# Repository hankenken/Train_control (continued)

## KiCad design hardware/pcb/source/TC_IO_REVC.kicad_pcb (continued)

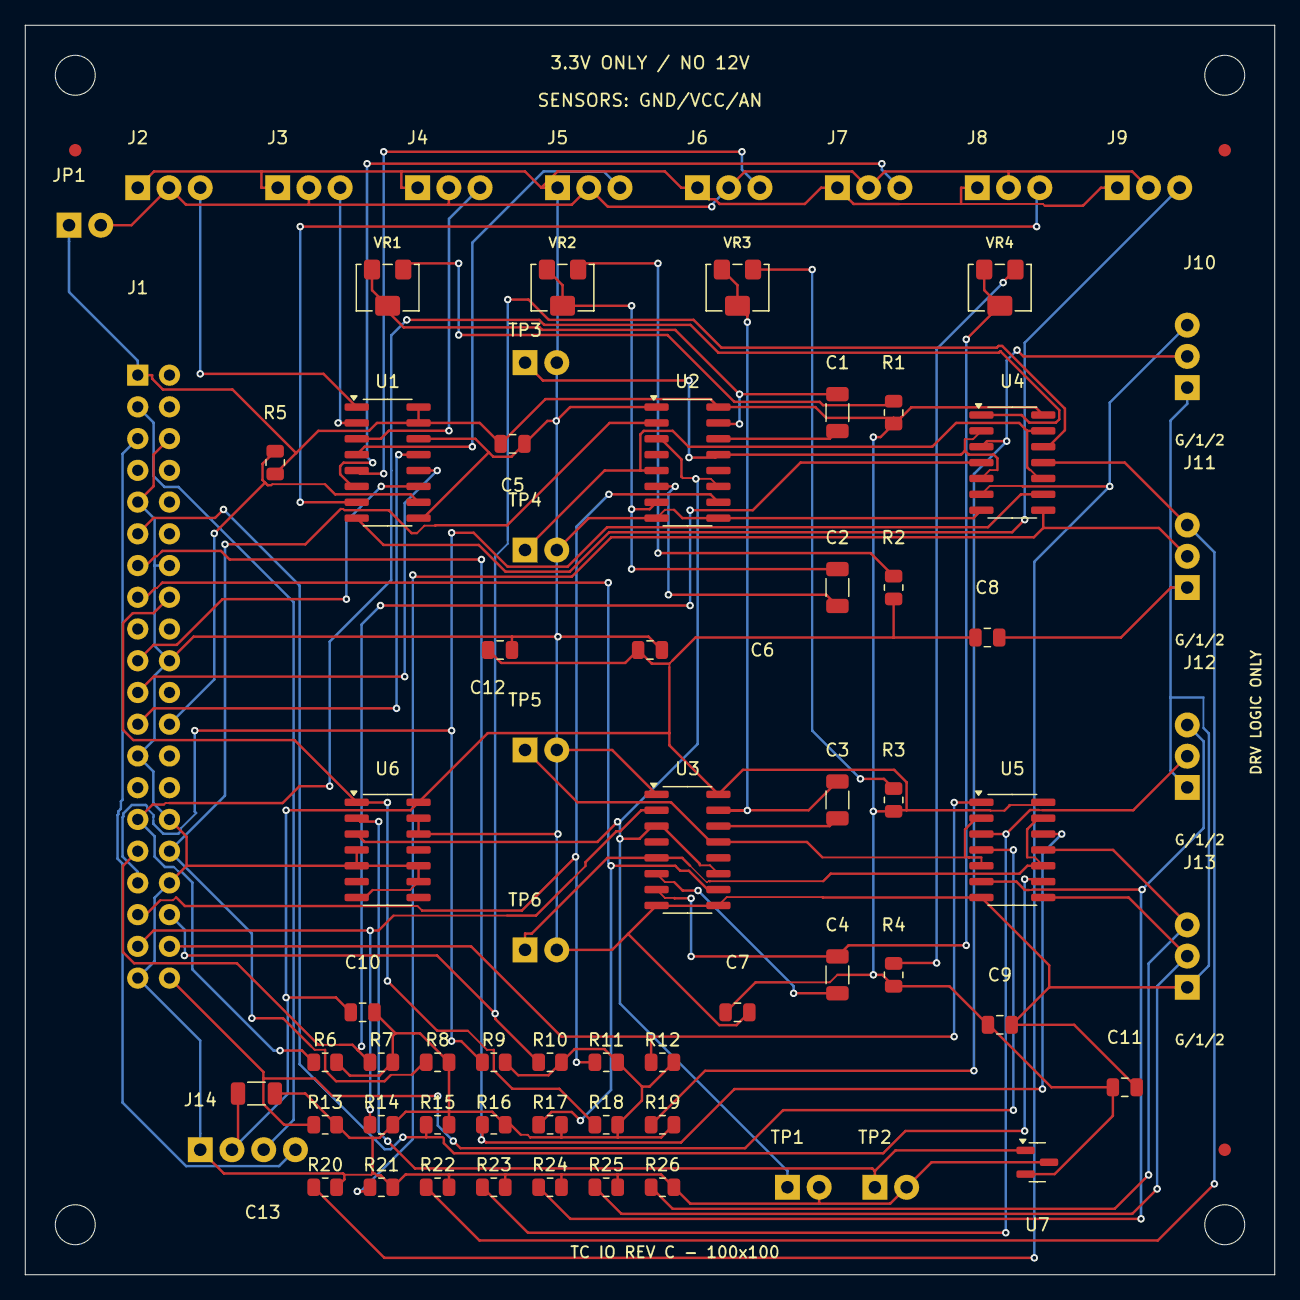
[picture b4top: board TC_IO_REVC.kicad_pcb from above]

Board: 2 copper layers, 100.0 x 100.0 mm, 78 parts (0 on the bottom side), 56 nets.

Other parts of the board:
FM1, FM2, FM3: Fiducial_1mm_Mask2mm
H1, H2, H3, H4: MountingHole_3.2mm_M3

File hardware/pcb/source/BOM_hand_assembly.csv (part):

Reference,Value_or_MPN,Footprint,Quantity,Notes,Populate
J1,WIRE_PADS_NO_COMPONENT,TC_Wire:WirePads_2x20_P2.54,0,Plated wire/test pads only. No connector or header component is fitted.,no
J2,WIRE_PADS_NO_COMPONENT,TC_Wire:WirePads_1x03_P2.50,0,Plated wire/test pads only. No connector or header component is fitted.,no
J3,WIRE_PADS_NO_COMPONENT,TC_Wire:WirePads_1x03_P2.50,0,Plated wire/test pads only. No connector or header component is fitted.,no
J4,WIRE_PADS_NO_COMPONENT,TC_Wire:WirePads_1x03_P2.50,0,Plated wire/test pads only. No connector or header component is fitted.,no
J5,WIRE_PADS_NO_COMPONENT,TC_Wire:WirePads_1x03_P2.50,0,Plated wire/test pads only. No connector or header component is fitted.,no
J6,WIRE_PADS_NO_COMPONENT,TC_Wire:WirePads_1x03_P2.50,0,Plated wire/test pads only. No connector or header component is fitted.,no
J7,WIRE_PADS_NO_COMPONENT,TC_Wire:WirePads_1x03_P2.50,0,Plated wire/test pads only. No connector or header component is fitted.,no
J8,WIRE_PADS_NO_COMPONENT,TC_Wire:WirePads_1x03_P2.50,0,Plated wire/test pads only. No connector or header component is fitted.,no
J9,WIRE_PADS_NO_COMPONENT,TC_Wire:WirePads_1x03_P2.50,0,Plated wire/test pads only. No connector or header component is fitted.,no
JP1,WIRE_PADS_NO_COMPONENT,TC_Wire:WirePads_1x02_P2.54,0,Plated wire/test pads only. No connector or header component is fitted.,no
U1,MCP3008T-I/SL,Package_SO:SOIC-16_3.9x9.9mm_P1.27mm,1,"10-bit ADC, 3.3V supply/reference; sensor outputs must stay within 0..3.3V",yes
U2,CD74HC221M96,Package_SO:SOIC-16_3.9x9.9mm_P1.27mm,1,"HC, NOT LS/HCT. Timing RC unverified at 3.3V: measure before load connection",yes
U3,CD74HC221M96,Package_SO:SOIC-16_3.9x9.9mm_P1.27mm,1,"HC, NOT LS/HCT. Timing RC unverified at 3.3V: measure before load connection",yes
U4,SN74HC08DR,Package_SO:SOIC-14_3.9x8.7mm_P1.27mm,1,,yes
U5,SN74HC08DR,Package_SO:SOIC-14_3.9x8.7mm_P1.27mm,1,,yes
U6,SN74HC08DR,Package_SO:SOIC-14_3.9x8.7mm_P1.27mm,1,,yes
U7,MCP100T-300I/TT,Package_TO_SOT_SMD:SOT-23,1,"RESET_N=pin1,VDD=pin2,VSS=pin3. Manufacturer/package pinout must be independently checked",yes
R6,10k_1%,Resistor_SMD:R_0805_2012Metric,1,Individual SMT pulldown replacing the former SIP resistor networks,yes
R7,10k_1%,Resistor_SMD:R_0805_2012Metric,1,Individual SMT pulldown replacing the former SIP resistor networks,yes
R8,10k_1%,Resistor_SMD:R_0805_2012Metric,1,Individual SMT pulldown replacing the former SIP resistor networks,yes
R9,10k_1%,Resistor_SMD:R_0805_2012Metric,1,Individual SMT pulldown replacing the former SIP resistor networks,yes
R10,10k_1%,Resistor_SMD:R_0805_2012Metric,1,Individual SMT pulldown replacing the former SIP resistor networks,yes
R11,10k_1%,Resistor_SMD:R_0805_2012Metric,1,Individual SMT pulldown replacing the former SIP resistor networks,yes
R12,10k_1%,Resistor_SMD:R_0805_2012Metric,1,Individual SMT pulldown replacing the former SIP resistor networks,yes
R13,10k_1%,Resistor_SMD:R_0805_2012Metric,1,Individual SMT pulldown replacing the former SIP resistor networks,yes
R14,10k_1%,Resistor_SMD:R_0805_2012Metric,1,Individual SMT pulldown replacing the former SIP resistor networks,yes
R15,10k_1%,Resistor_SMD:R_0805_2012Metric,1,Individual SMT pulldown replacing the former SIP resistor networks,yes
R16,10k_1%,Resistor_SMD:R_0805_2012Metric,1,Individual SMT pulldown replacing the former SIP resistor networks,yes
R17,10k_1%,Resistor_SMD:R_0805_2012Metric,1,Individual SMT pulldown replacing the former SIP resistor networks,yes
R18,10k_1%,Resistor_SMD:R_0805_2012Metric,1,Individual SMT pulldown replacing the former SIP resistor networks,yes
R19,10k_1%,Resistor_SMD:R_0805_2012Metric,1,Individual SMT pulldown replacing the former SIP resistor networks,yes
R20,10k_1%,Resistor_SMD:R_0805_2012Metric,1,Individual SMT pulldown replacing the former SIP resistor networks,yes
R21,10k_1%,Resistor_SMD:R_0805_2012Metric,1,Individual SMT pulldown replacing the former SIP resistor networks,yes
R22,10k_1%,Resistor_SMD:R_0805_2012Metric,1,Individual SMT pulldown replacing the former SIP resistor networks,yes
R23,10k_1%,Resistor_SMD:R_0805_2012Metric,1,Individual SMT pulldown replacing the former SIP resistor networks,yes
R24,10k_1%,Resistor_SMD:R_0805_2012Metric,1,Individual SMT pulldown replacing the former SIP resistor networks,yes
R25,10k_1%,Resistor_SMD:R_0805_2012Metric,1,Individual SMT pulldown replacing the former SIP resistor networks,yes
R26,10k_1%,Resistor_SMD:R_0805_2012Metric,1,Individual SMT pulldown replacing the former SIP resistor networks,yes
R1,150k_1%,Resistor_SMD:R_0805_2012Metric,1,,yes
VR1,3224W-1-104E,Potentiometer_SMD:Potentiometer_Bourns_3224W_Vertical,1,"100k multi-turn trimmer, series with 150k. Wiper pin2 tied to pin3; verify CW direction and pulse width on bench",yes
C1,470nF_10%_X7R_50V,Capacitor_SMD:C_1206_3216Metric,1,"Floating timing MLCC: CEXT to RCEXT. Verify DC bias, temperature and actual pulse width; no guaranteed timing limit",yes
R2,150k_1%,Resistor_SMD:R_0805_2012Metric,1,,yes
VR2,3224W-1-104E,Potentiometer_SMD:Potentiometer_Bourns_3224W_Vertical,1,"100k multi-turn trimmer, series with 150k. Wiper pin2 tied to pin3; verify CW direction and pulse width on bench",yes
C2,470nF_10%_X7R_50V,Capacitor_SMD:C_1206_3216Metric,1,"Floating timing MLCC: CEXT to RCEXT. Verify DC bias, temperature and actual pulse width; no guaranteed timing limit",yes
R3,150k_1%,Resistor_SMD:R_0805_2012Metric,1,,yes
VR3,3224W-1-104E,Potentiometer_SMD:Potentiometer_Bourns_3224W_Vertical,1,"100k multi-turn trimmer, series with 150k. Wiper pin2 tied to pin3; verify CW direction and pulse width on bench",yes
C3,470nF_10%_X7R_50V,Capacitor_SMD:C_1206_3216Metric,1,"Floating timing MLCC: CEXT to RCEXT. Verify DC bias, temperature and actual pulse width; no guaranteed timing limit",yes
R4,150k_1%,Resistor_SMD:R_0805_2012Metric,1,,yes
VR4,3224W-1-104E,Potentiometer_SMD:Potentiometer_Bourns_3224W_Vertical,1,"100k multi-turn trimmer, series with 150k. Wiper pin2 tied to pin3; verify CW direction and pulse width on bench",yes
C4,470nF_10%_X7R_50V,Capacitor_SMD:C_1206_3216Metric,1,"Floating timing MLCC: CEXT to RCEXT. Verify DC bias, temperature and actual pulse width; no guaranteed timing limit",yes
C5,100nF_X7R_50V,Capacitor_SMD:C_0805_2012Metric,1,IC bypass; keep close,yes
C6,100nF_X7R_50V,Capacitor_SMD:C_0805_2012Metric,1,IC bypass; keep close,yes
C7,100nF_X7R_50V,Capacitor_SMD:C_0805_2012Metric,1,IC bypass; keep close,yes
C8,100nF_X7R_50V,Capacitor_SMD:C_0805_2012Metric,1,IC bypass; keep close,yes
C9,100nF_X7R_50V,Capacitor_SMD:C_0805_2012Metric,1,IC bypass; keep close,yes
C10,100nF_X7R_50V,Capacitor_SMD:C_0805_2012Metric,1,IC bypass; keep close,yes
C11,100nF_X7R_50V,Capacitor_SMD:C_0805_2012Metric,1,IC bypass; keep close,yes
C12,100nF_X7R_50V,Capacitor_SMD:C_0805_2012Metric,1,ADC reference bypass,yes
C13,10uF_X7R_25V,Capacitor_SMD:C_1206_3216Metric,1,Nonpolar MLCC bulk bypass; check effective capacitance,yes
R5,10k_1%,Resistor_SMD:R_0805_2012Metric,1,,yes
J10,WIRE_PADS_NO_COMPONENT,TC_Wire:WirePads_1x03_P2.50,0,Plated wire/test pads only. No connector or header component is fitted.,no
J11,WIRE_PADS_NO_COMPONENT,TC_Wire:WirePads_1x03_P2.50,0,Plated wire/test pads only. No connector or header component is fitted.,no
J12,WIRE_PADS_NO_COMPONENT,TC_Wire:WirePads_1x03_P2.50,0,Plated wire/test pads only. No connector or header component is fitted.,no
J13,WIRE_PADS_NO_COMPONENT,TC_Wire:WirePads_1x03_P2.50,0,Plated wire/test pads only. No connector or header component is fitted.,no
J14,WIRE_PADS_NO_COMPONENT,TC_Wire:WirePads_1x04_P2.54,0,Plated wire/test pads only. No connector or header component is fitted.,no
TP1,WIRE_PADS_NO_COMPONENT,TC_Wire:WirePads_1x02_P2.54,0,Plated wire/test pads only. No connector or header component is fitted.,no
TP2,WIRE_PADS_NO_COMPONENT,TC_Wire:WirePads_1x02_P2.54,0,Plated wire/test pads only. No connector or header component is fitted.,no
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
